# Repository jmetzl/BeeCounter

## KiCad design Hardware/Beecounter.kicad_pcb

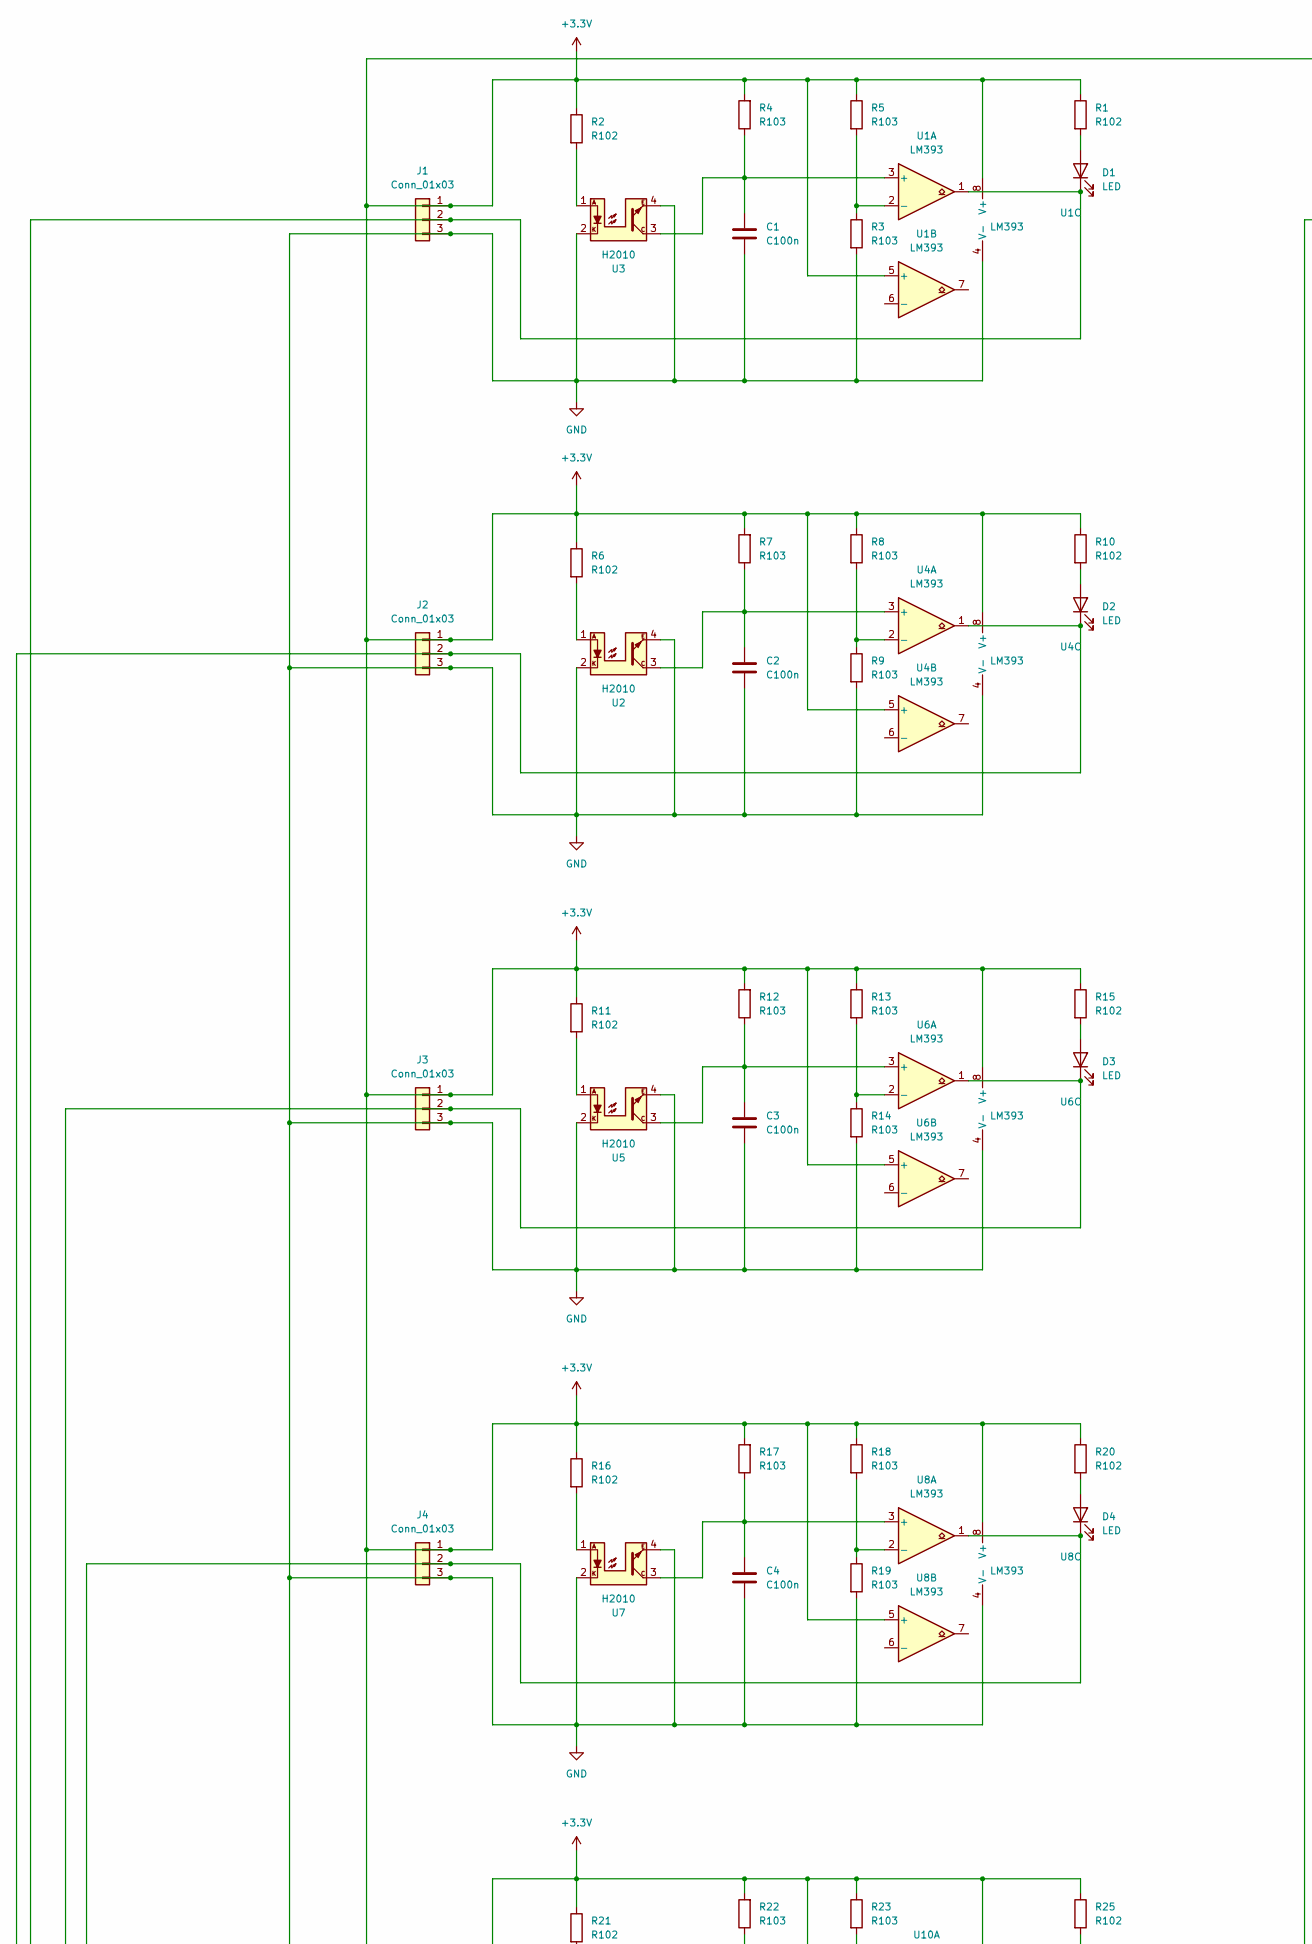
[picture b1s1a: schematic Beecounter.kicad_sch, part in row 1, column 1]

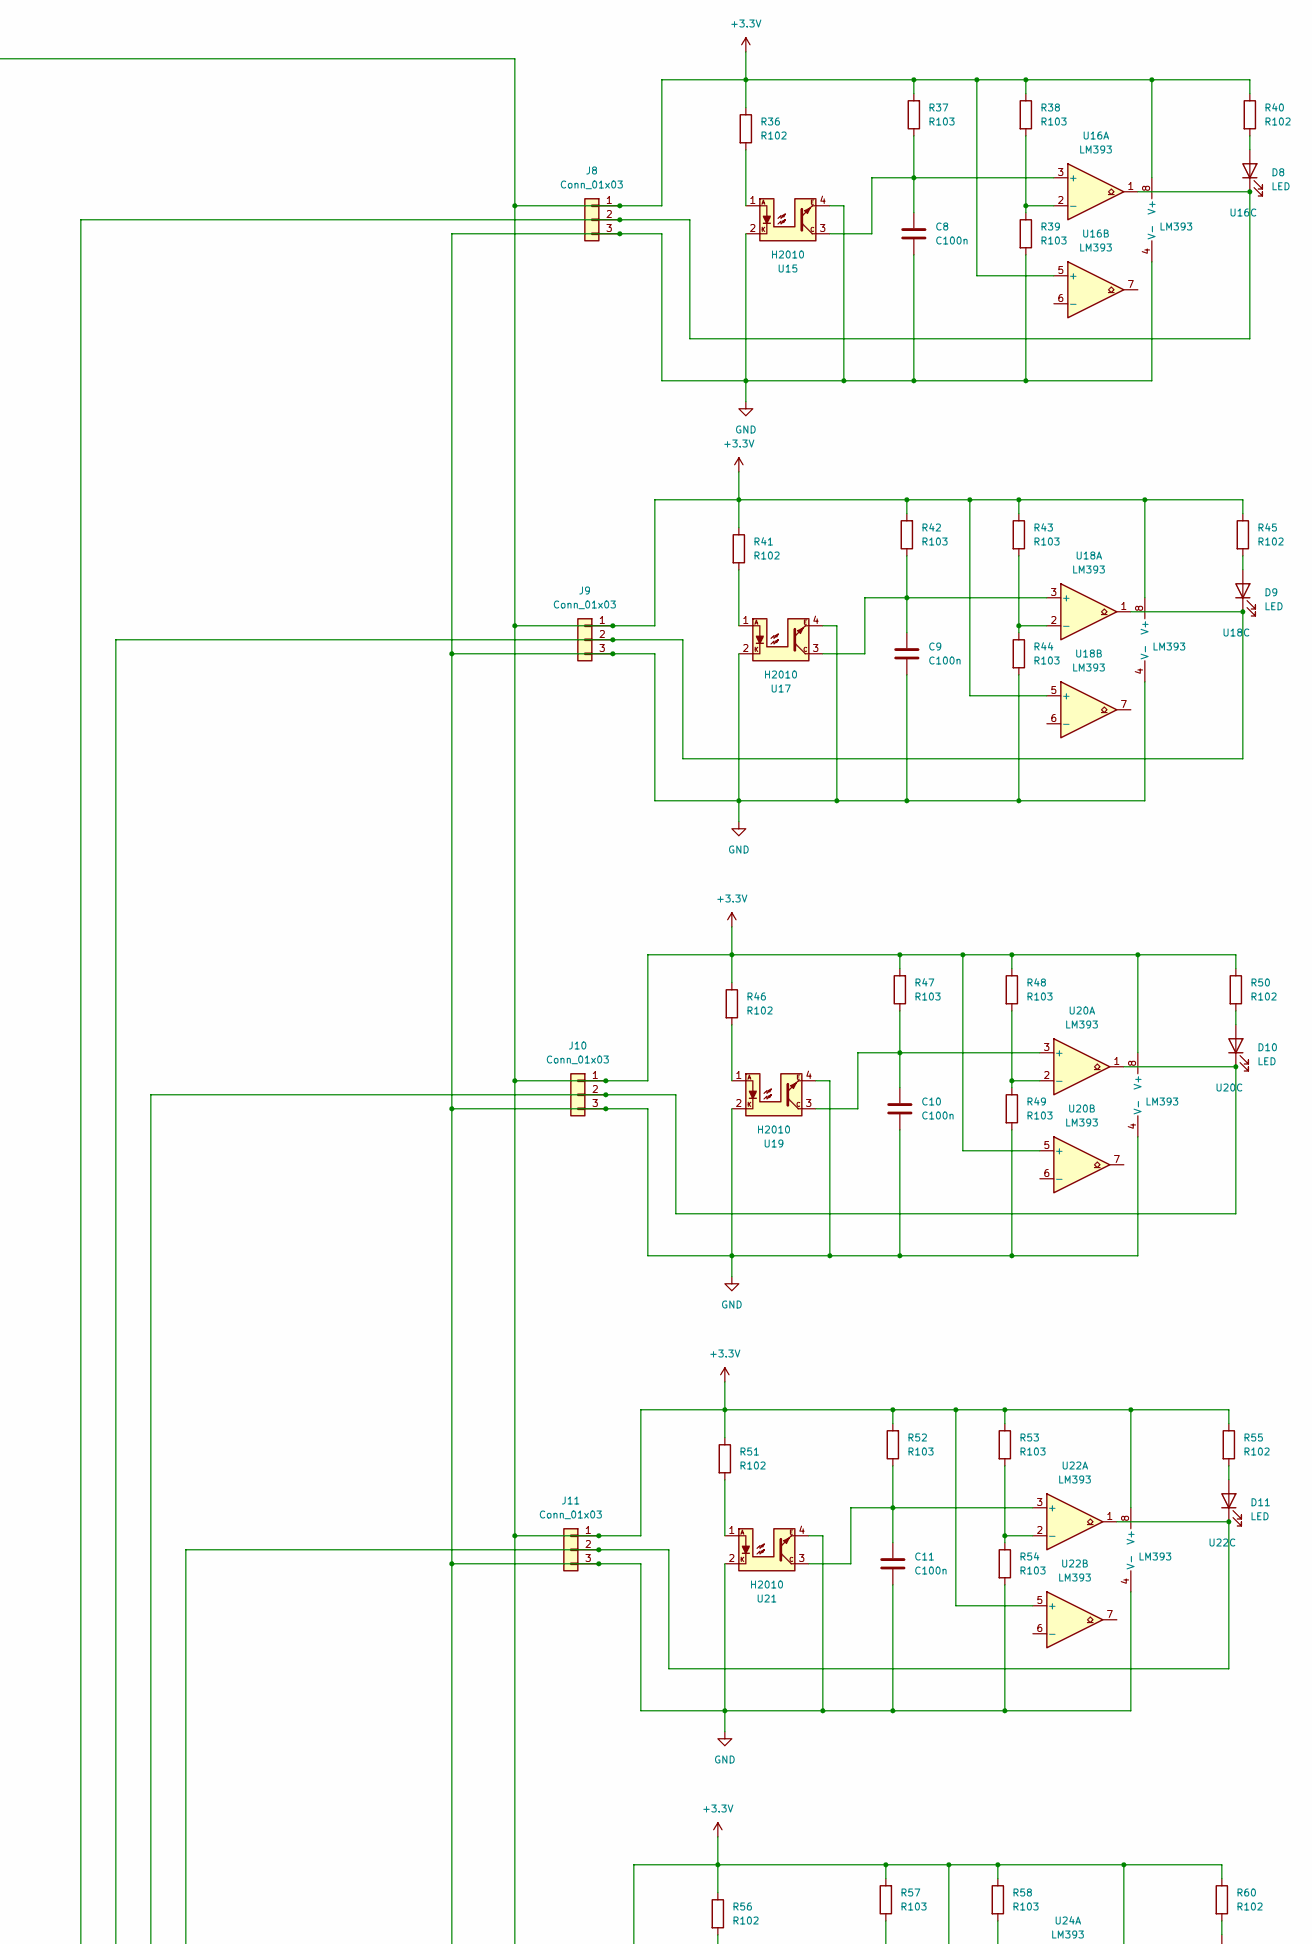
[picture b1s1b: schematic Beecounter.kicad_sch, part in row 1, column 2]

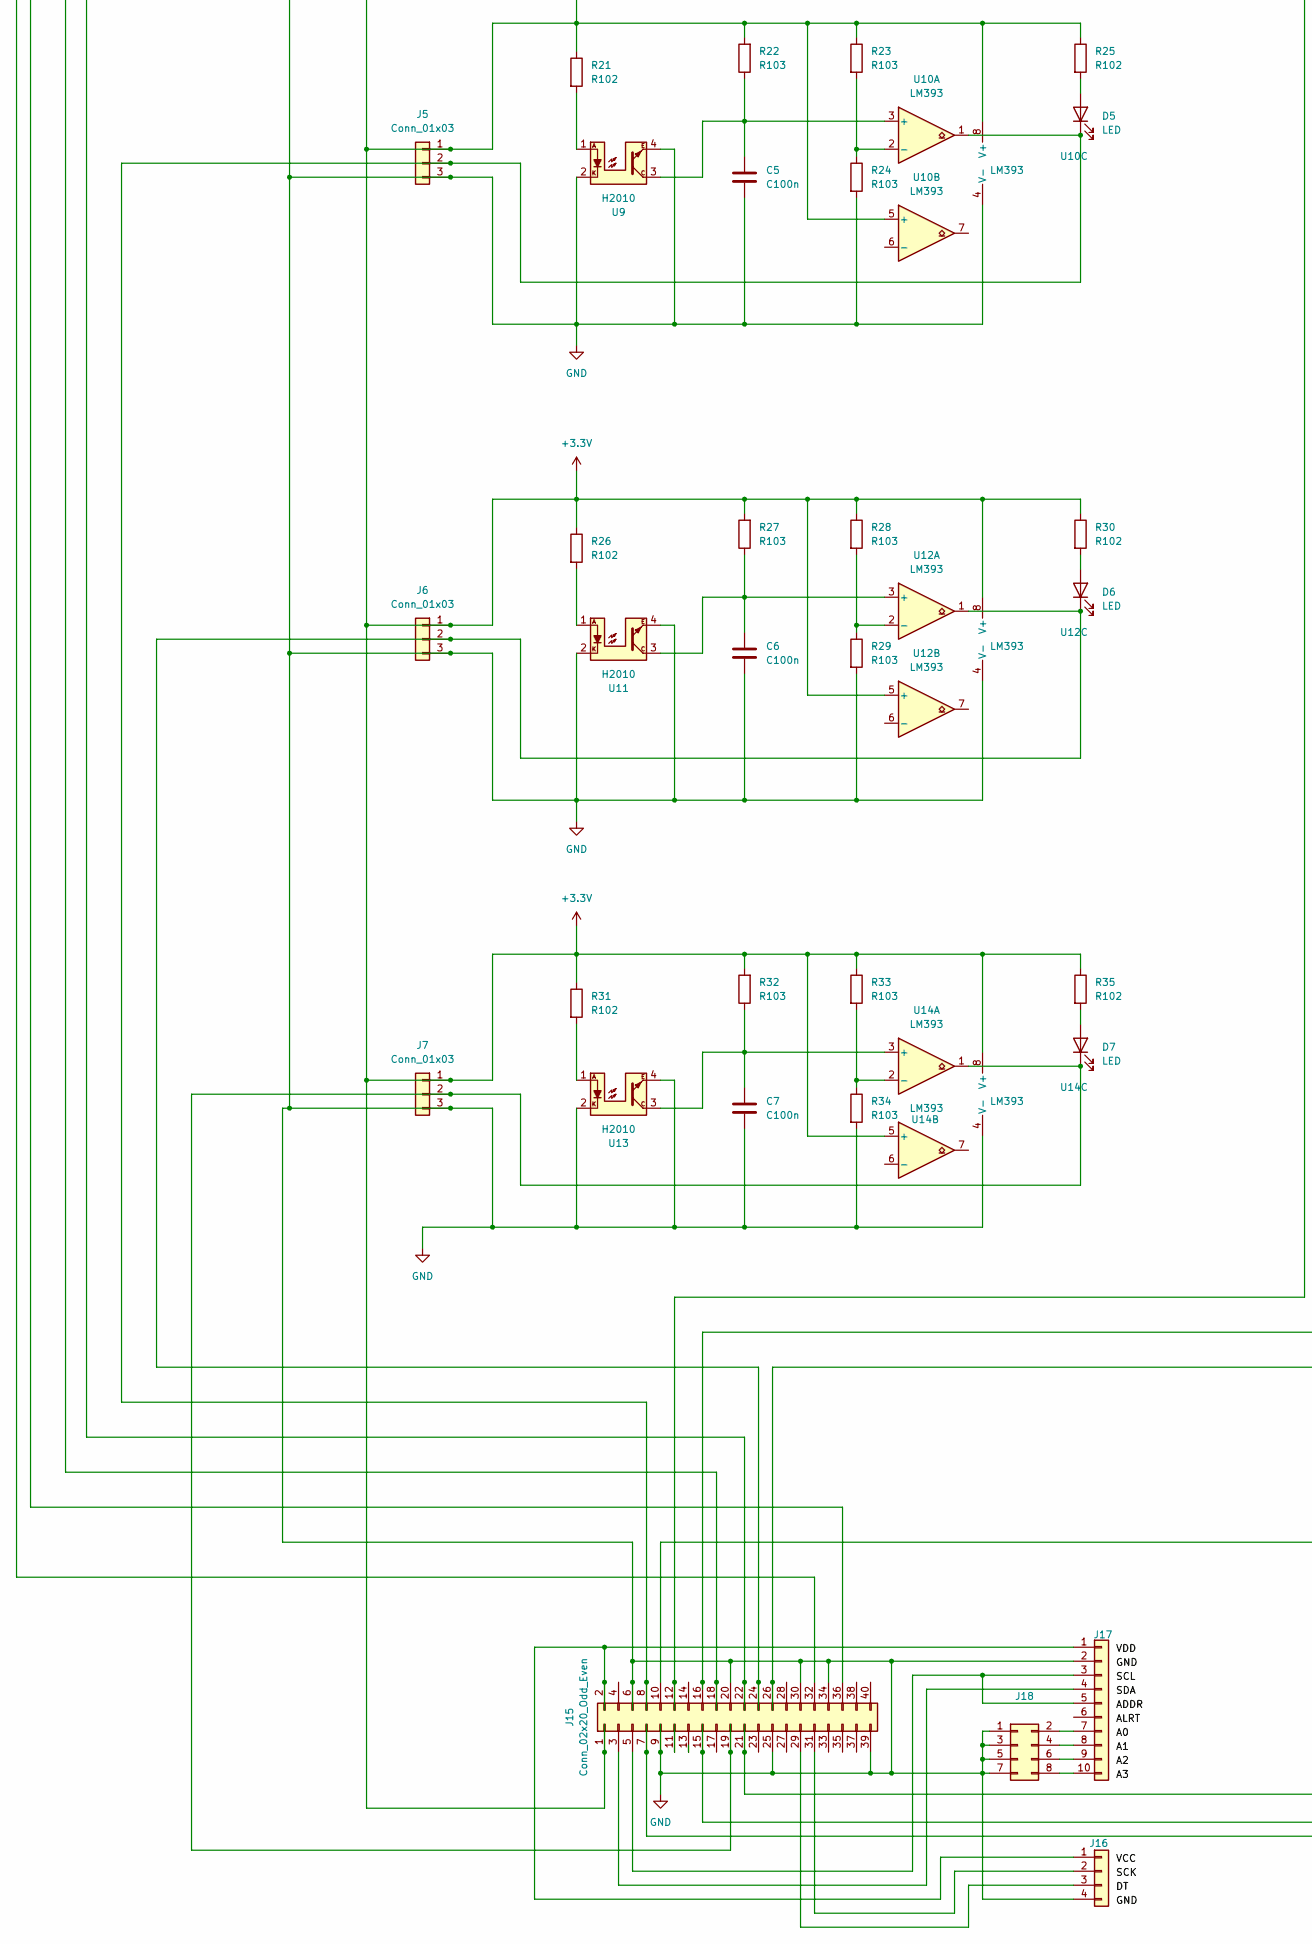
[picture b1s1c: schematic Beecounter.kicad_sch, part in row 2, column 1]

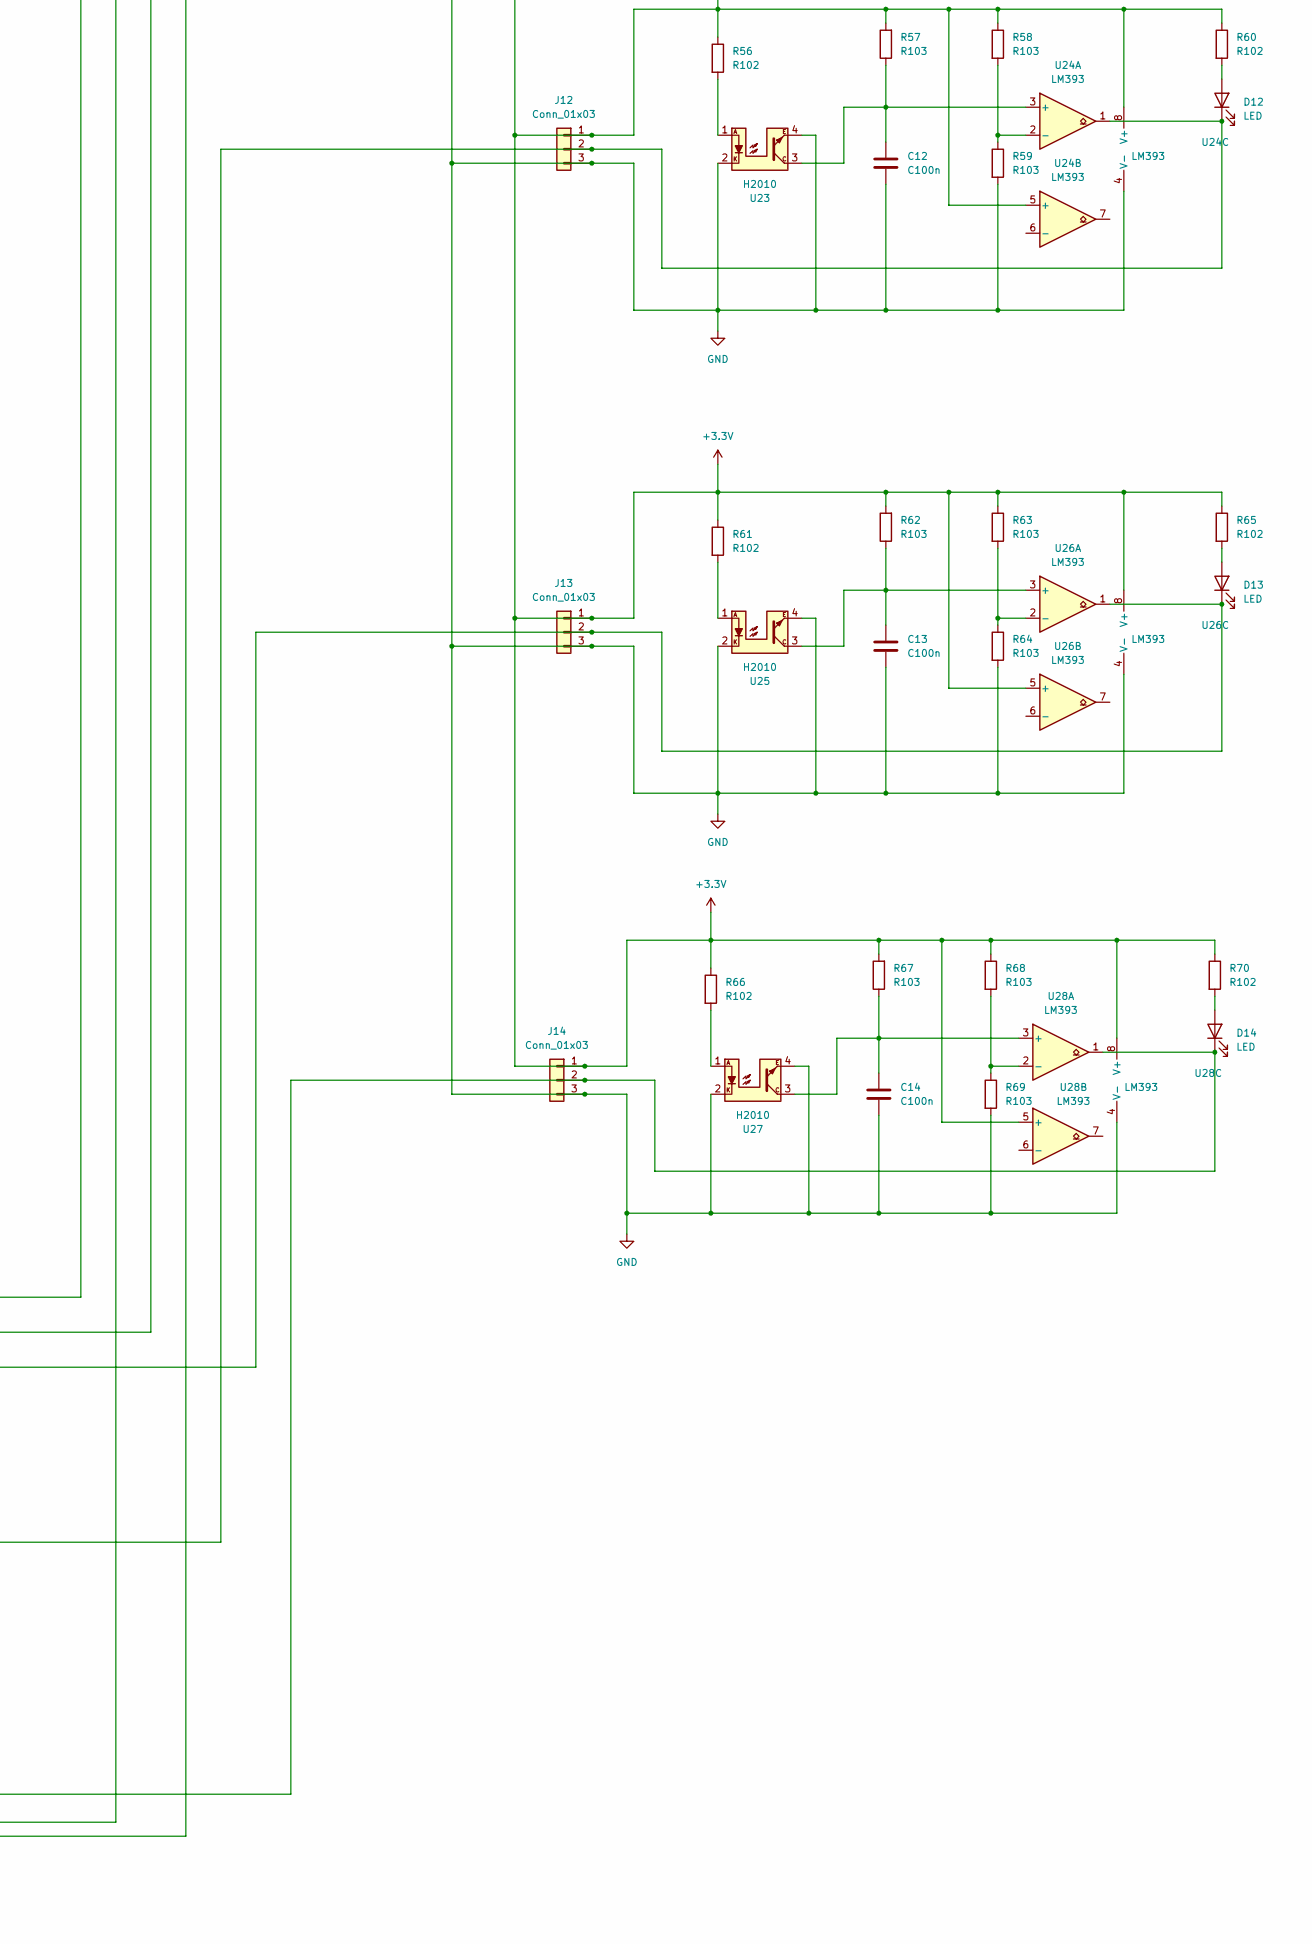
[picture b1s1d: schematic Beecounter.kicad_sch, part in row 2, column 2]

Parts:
C1, C2, C3, C4, C5, C6, C7, C8, C9, C10, C11, C12, C13, C14: C100n; C_0603_1608Metric_Pad1.08x0.95mm_HandSolder
D1, D2, D3, D4, D5, D6, D7, D8, D9, D10, D11, D12, D13, D14: LED; LED_0603_1608Metric_Pad1.05x0.95mm_HandSolder
J1, J2, J3, J4, J5, J6, J7, J8, J9, J10, J11, J12, J13, J14: Conn_01x03; PinHeader_1x03_P2.54mm_Vertical
J15: Conn_02x20_Odd_Even; PinSocket_2x20_P2.54mm_Vertical
J16: Conn_01x04; PinSocket_1x04_P2.54mm_Vertical
J17: Conn_01x10; PinHeader_1x10_P2.54mm_Vertical
J18: Conn_02x04_Odd_Even
R1, R2, R6, R10, R11, R15, R16, R20, R21, R25, R26, R30, R31, R35, R36, R40, R41, R45, R46, R50, R51, R55, R56, R60, R61, R65, R66, R70: R102; R_0603_1608Metric_Pad0.98x0.95mm_HandSolder
R3, R4, R5, R7, R8, R9, R12, R13, R14, R17, R18, R19, R22, R23, R24, R27, R28, R29, R32, R33, R34, R37, R38, R39, R42, R43, R44, R47, R48, R49, R52, R53, R54, R57, R58, R59, R62, R63, R64, R67, R68, R69: R103; R_0603_1608Metric_Pad0.98x0.95mm_HandSolder
U1, U4, U6, U8, U10, U12, U14, U16, U18, U20, U22, U24, U26, U28: LM393; SOIC-8_3.9x4.9mm_P1.27mm
U2, U3, U5, U7, U9, U11, U13, U15, U17, U19, U21, U23, U25, U27: H2010; Gabellichtschranke 10mm

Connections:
+3.3V: J1.1, J2.1, J3.1, J4.1, J5.1, J6.1, J7.1, J8.1, J9.1, J10.1, J11.1, J12.1, J13.1, J14.1, J15.1, R1.1, R2.1, R4.2, R5.1, R6.1, R7.2, R8.1, R10.1, R11.1, R12.2, R13.1, R15.1, R16.1, R17.2, R18.1, R20.1, R21.1, R22.2, R23.1, R25.1, R26.1, R27.2, R28.1, R30.1, R31.1, R32.2, R33.1, R35.1, R36.1, R37.2, R38.1, R40.1, R41.1, R42.2, R43.1, R45.1, R46.1, R47.2, R48.1, R50.1, R51.1, R52.2, R53.1, R55.1, R56.1, R57.2, R58.1, R60.1, R61.1, R62.2, R63.1, R65.1, R66.1, R67.2, R68.1, R70.1, U1.5 (+), U1.8 (V+), U4.5 (+), U4.8 (V+), U6.5 (+), U6.8 (V+), U8.5 (+), U8.8 (V+), U10.5 (+), U10.8 (V+), U12.5 (+), U12.8 (V+), U14.5 (+), U14.8 (V+), U16.5 (+), U16.8 (V+), U18.5 (+), U18.8 (V+), U20.5 (+), U20.8 (V+), U22.5 (+), U22.8 (V+), U24.5 (+), U24.8 (V+), U26.5 (+), U26.8 (V+), U28.5 (+), U28.8 (V+)
GND: C1.2, C2.2, C3.2, C4.2, C5.2, C6.2, C7.2, C8.2, C9.2, C10.2, C11.2, C12.2, C13.2, C14.2, J1.3, J2.3, J3.3, J4.3, J5.3, J6.3, J7.3, J8.3, J9.3, J10.3, J11.3, J12.3, J13.3, J14.3, J15.6, J15.9, J15.20, J15.25, J15.30, J15.34, J15.39, J16.4, J17.2, J18.1, J18.3, J18.5, J18.7, R3.2, R9.2, R14.2, R19.2, R24.2, R29.2, R34.2, R39.2, R44.2, R49.2, R54.2, R59.2, R64.2, R69.2, U1.4 (V-), U2.2, U2.4, U3.2, U3.4, U4.4 (V-), U5.2, U5.4, U6.4 (V-), U7.2, U7.4, U8.4 (V-), U9.2, U9.4, U10.4 (V-), U11.2, U11.4, U12.4 (V-), U13.2, U13.4, U14.4 (V-), U15.2, U15.4, U16.4 (V-), U17.2, U17.4, U18.4 (V-), U19.2, U19.4, U20.4 (V-), U21.2, U21.4, U22.4 (V-), U23.2, U23.4, U24.4 (V-), U25.2, U25.4, U26.4 (V-), U27.2, U27.4, U28.4 (V-)
unnamed: D1.2 (A), R1.2
unnamed: D1.1 (K), J1.2, J15.36, U1.1
unnamed: D2.2 (A), R10.2
unnamed: D2.1 (K), J2.2, J15.32, U4.1
unnamed: D3.2 (A), R15.2
unnamed: D3.1 (K), J3.2, J15.18, U6.1
unnamed: D4.2 (A), R20.2
unnamed: D4.1 (K), J4.2, J15.22, U8.1
unnamed: D5.2 (A), R25.2
unnamed: D5.1 (K), J5.2, J15.8, U10.1
unnamed: D6.2 (A), R30.2
unnamed: D6.1 (K), J6.2, J15.24, U12.1
unnamed: D7.2 (A), R35.2
unnamed: D7.1 (K), J7.2, J15.19, U14.1
unnamed: D8.2 (A), R40.2
unnamed: D8.1 (K), J8.2, J15.12, U16.1
unnamed: D9.2 (A), R45.2
unnamed: D9.1 (K), J9.2, J15.15, U18.1
unnamed: D10.2 (A), R50.2
unnamed: D10.1 (K), J10.2, J15.16, U20.1
unnamed: D11.2 (A), R55.2
unnamed: D11.1 (K), J11.2, J15.7, U22.1
unnamed: D12.2 (A), R60.2
unnamed: D12.1 (K), J12.2, J15.10, U24.1
unnamed: D13.2 (A), R65.2
unnamed: D13.1 (K), J13.2, J15.26, U26.1
unnamed: D14.2 (A), R70.2
unnamed: D14.1 (K), J14.2, J15.21, U28.1
unnamed: J15.2, J16.1, J17.1
unnamed: J15.3, J17.4
unnamed: J15.5, J17.3, J17.5
unnamed: J15.29, J16.3
unnamed: J15.31, J16.2
unnamed: J17.7, J18.2
unnamed: J17.8, J18.4
unnamed: J17.9, J18.6
unnamed: J17.10, J18.8
unnamed: R2.2, U3.1
unnamed: R6.2, U2.1
unnamed: R11.2, U5.1
unnamed: R16.2, U7.1
unnamed: R21.2, U9.1
unnamed: R26.2, U11.1
unnamed: R31.2, U13.1
unnamed: R36.2, U15.1
unnamed: R41.2, U17.1
unnamed: R46.2, U19.1
unnamed: R51.2, U21.1
unnamed: R56.2, U23.1
unnamed: R61.2, U25.1
unnamed: R66.2, U27.1
unnamed: C1.1, R4.1, U1.3 (+), U3.3
unnamed: R3.1, R5.2, U1.2 (-)
unnamed: C2.1, R7.1, U2.3, U4.3 (+)
unnamed: R8.2, R9.1, U4.2 (-)
unnamed: C3.1, R12.1, U5.3, U6.3 (+)
unnamed: R13.2, R14.1, U6.2 (-)
unnamed: C4.1, R17.1, U7.3, U8.3 (+)
unnamed: R18.2, R19.1, U8.2 (-)
unnamed: C5.1, R22.1, U9.3, U10.3 (+)
unnamed: R23.2, R24.1, U10.2 (-)
unnamed: C6.1, R27.1, U11.3, U12.3 (+)
unnamed: R28.2, R29.1, U12.2 (-)
unnamed: C7.1, R32.1, U13.3, U14.3 (+)
unnamed: R33.2, R34.1, U14.2 (-)
unnamed: C8.1, R37.1, U15.3, U16.3 (+)
unnamed: R38.2, R39.1, U16.2 (-)
unnamed: C9.1, R42.1, U17.3, U18.3 (+)
unnamed: R43.2, R44.1, U18.2 (-)
unnamed: C10.1, R47.1, U19.3, U20.3 (+)
unnamed: R48.2, R49.1, U20.2 (-)
unnamed: C11.1, R52.1, U21.3, U22.3 (+)
unnamed: R53.2, R54.1, U22.2 (-)
unnamed: C12.1, R57.1, U23.3, U24.3 (+)
unnamed: R58.2, R59.1, U24.2 (-)
unnamed: C13.1, R62.1, U25.3, U26.3 (+)
unnamed: R63.2, R64.1, U26.2 (-)
unnamed: C14.1, R67.1, U27.3, U28.3 (+)
unnamed: R68.2, R69.1, U28.2 (-)

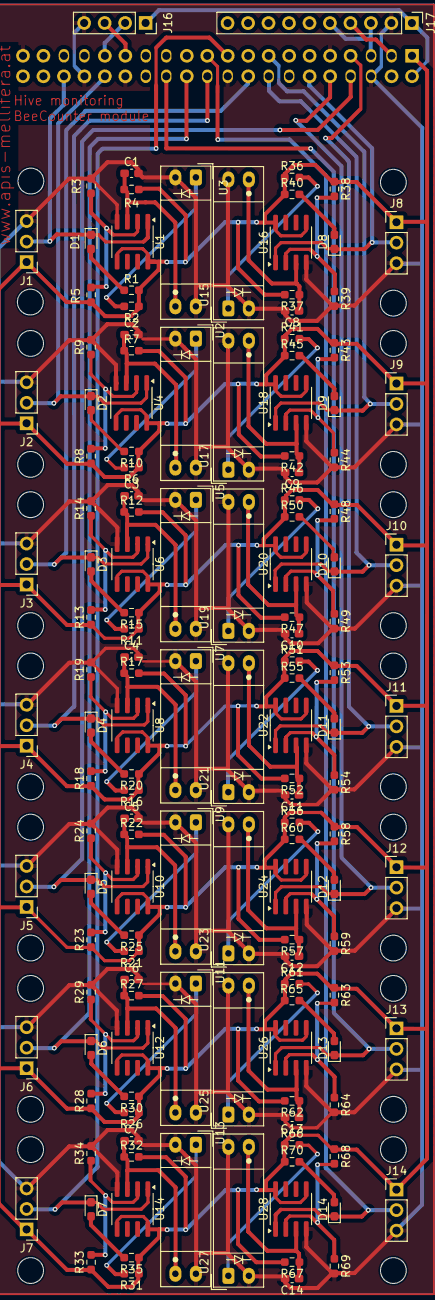
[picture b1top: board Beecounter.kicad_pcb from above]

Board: 2 copper layers, 143 parts (1 on the bottom side), 77 nets.

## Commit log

2024-06-09 Initial checkin
2024-06-09 Updated line width to 0.4mm
2024-12-16 First production prototype version
2024-12-16 Added outlines for top PCB plate
2024-12-16 Added description file on how to cutout regions
2024-12-16 Top PCB layer
2024-12-18 Added documentation on how to import a drawing from Corel Draw into CorelCad with inches
2024-12-18 Corrected typo
2024-12-18 Added frequently used commands
2024-12-18 Added comment on how to change drawing units from 'inches' to 'mm'
2024-12-18 Added initial draft for chassis
2024-12-19 Added Beecounter entrance
2024-12-19 Added Beecounter entrance (with entry arcs)
2024-12-19 First printable version
2024-12-20 Beecounter without subtract of inner volumne
2024-12-22 Disk image for Raspberry Pi BeeCounter
2024-12-22 Added documentation for Raspberry Pi
2024-12-28 Added documentation for VNC Server installation
2024-12-28 First working Python program (Except for to entrance - not working)
2024-12-29 Added documentation of web-server setup
2024-12-30 Added documentation for Maria DB installation
2024-12-30 Added Samba configuration
2024-12-30 Added phpmyadmin installation
2024-12-30 Fix issue - port 3306 not open for public access
2024-12-30 Created initial database schema
2024-12-31 Added documentation for JDK17 installation
2024-12-31 Folderstructure change
2024-12-31 Renamed table
2024-12-31 Initial BeeCounterDaemon project commit
2024-12-31 Initial EclipseLink persistence layer generation
2024-12-31 Added named queries for entities
2024-12-31 Established working DB connection
2024-12-31 Working named queryies
2025-01-01 Query all core tables
2025-01-01 Implemented BusinessServices and JUnit tests
2025-01-01 Added first draft of Pi4j implementation
2025-01-01 Added sequences
2025-01-01 Added CustomDigitalStateChangeListener to listen for Light Barrier crossing events and store date/time stamp in BEE_TRAFFIC table
2025-01-01 Added detailed logging
2025-01-02 Create FAT Jar with all dependencies using Maven
2025-01-02 Using maven-shade-plugin to create FAT JAR
2025-01-02 Using maven-assembly-plugin to create FAT JAR 'mvn clean package assembly:single' => working version
2025-01-02 Registered CustomDigitalStateChangeListener
2025-01-02 Initialize digital input as PULL DOWN
2025-01-02 Initialize digital input as PULL UP
2025-01-02 Added generic DigitalStateChangeListener
2025-01-02 Changed endless loop to wait for 100ms
2025-01-02 Added GPIO PIN
2025-01-02 Added persistence layer changes for GPIO pin
2025-01-02 Usage of GPIO pin number instead of port number as suggested by Copilot
2025-01-02 Removed resistor PULL configuration
2025-01-02 Added var
2025-01-02 Change DigitalInput configuration
2025-01-02 Refactoring of Board Information
2025-01-02 Added pi4j-library-pipgio
2025-01-02 Added pi4j-plugin-pipgio
2025-01-02 Removed keyword pigpio-digital-input
2025-01-02 Added DigitalStage
2025-01-02 Added PullResistance configuration
2025-01-02 Turn OFF PullResistance configuration
2025-01-02 PullResistance UP configuration
2025-01-03 Added output of registered instances
2025-01-03 Refactored modules
2025-01-03 Reverted refactoring
2025-01-03 Added documentation for system log and test python script
2025-01-03 Added daemon Python process for logging Light Barrier cross events.
2025-01-03 Change MySQL DB password
2025-01-03 Formatting issue
2025-01-03 Fixed typo
2025-01-03 Fixed formatting
2025-01-05 Set log level DEBUG
2025-01-18 Fix issue with entrance 5. Connected light barrier to pin 10 (GPIO16) instead of 9 (GND)
2025-01-18 Set power supply for light barriers to 3.3V
2025-01-18 Exchanged pin 16 and 18
2025-01-18 Connected GND pins
2025-01-18 Exchanged pin 13 with 32 and 11 with 36
2025-01-19 Added connector for HX711 (H-bridge) and ADC ADS1115
2025-01-19 Red layer 0.4mm
2025-01-25 Smaller outer boarders
2025-01-25 Removed measurement
2025-01-25 Generated GND area and Gerber files
2025-01-25 Set origin
2025-01-25 Removed backups
2025-01-25 Added persistence.xml
2025-01-25 Added FlatCam BeeCounter project
2025-01-25 Smaller pads for main connector
2025-01-25 Completed BeeCounter v1.1 from milling/drilling
2025-01-25 Red layer 0.5mm
2025-02-01 Corrected red layer
2025-02-01 Final version 1.1
2025-02-15 Added solder mask
2025-02-22 Added holder for Laser cutter => Solder mask creation
2025-03-14 Added first draft CorrelCad drawing
2025-03-15 Added first draft FreeCad drawing
2025-03-16 Updated pins/GPIO
2025-03-22 Initial drawing - Pfefferle boden
2025-03-22 Pfefferle bottom complete
2025-03-23 Schliesser vorne/hinten
2025-03-23 Boden komplett
2025-03-23 Boden inklusive - Lade unten
2025-03-23 Pfefferle Taunus Zarge - complete
2025-03-29 Added description on howto install Keyboard K810 on raspberry pi
2025-03-29 Added description on howto install Logitech mouse M308 on raspberry pi
